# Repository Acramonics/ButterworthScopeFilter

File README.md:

ScopeFilter
===========

Andrew Martin, Acramonics, January 2026
---------------------------------------

This ScopeFilter is designed for putting in front of an oscilloscope
when doing audio work where there is HF interference from computers,
etc. It is a simple Active Butterworth dual 2nd order filter with a
cutoff of 50kHz.

It is powered by a standard 9v wallwart with the power supply section
taken from the Elektor ESR meter giving positive and negative 4.5v
rails.

Filter component values are calculated from
https://www.changpuak.ch/electronics/Butterworth_Lowpass_active_24dB.php
and tweaked to standard values. As specified, the filter starts to cut
off at 40kHz.

The `LTSpice` directory contains an LTSpice simulation showing the
frequency response. The Kicad Spice simulator seems to have difficulty
with dual rail power supplies.

The `FrontPanelDesigner` directory contains a simple front panel
layout for use with a small aluminium case (W:3.25" H:1.25" x D:4").
The software is available from schaeffer-ag.de/en/front-panel-designer

I built the filter without Molex 254s for any of the wires except the
power input. This is the only one that comes from the back making it
convenient (with long enough wires) to be able to take off the front
panel (which is closely connected to the PCB) and unplug the power
from the board.

These images are generated by Kicad:

With the exception of the two 100nF caps, I also ended up building the
board with 5mm ceramic caps in place of the box film caps shown.

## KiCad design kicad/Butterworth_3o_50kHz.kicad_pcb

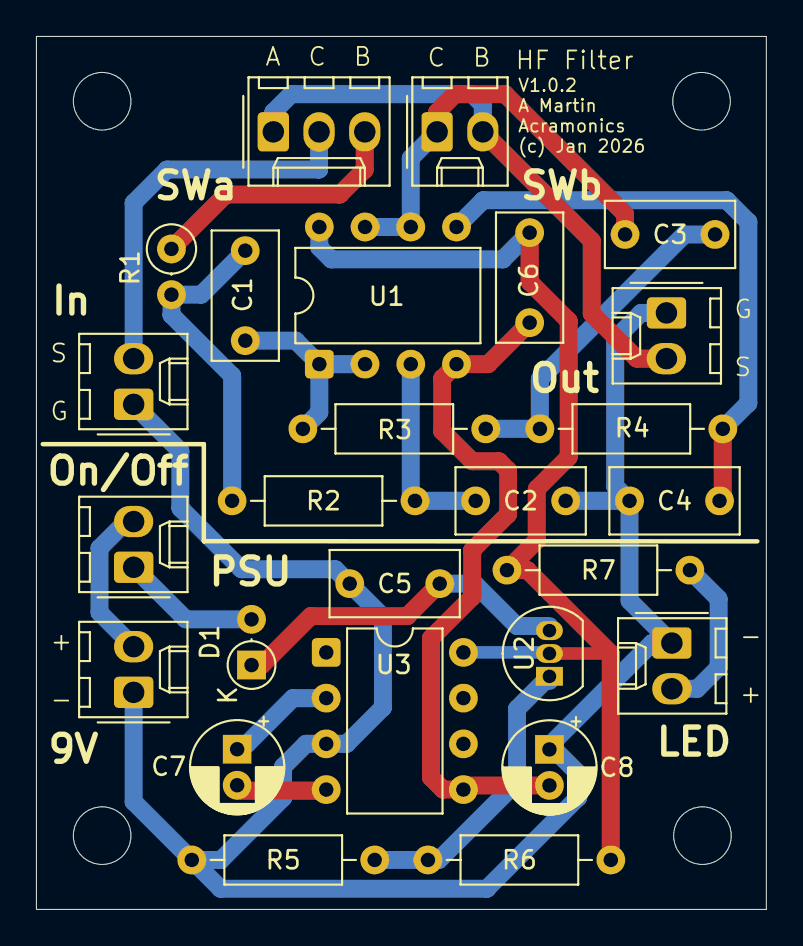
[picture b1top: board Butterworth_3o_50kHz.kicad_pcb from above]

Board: 2 copper layers, 40.6 x 48.5 mm, 26 parts (0 on the bottom side), 19 nets.

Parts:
C1, C2: 3.3nF; C_Rect_L7.0mm_W3.5mm_P5.00mm
C3: 8.2nF; C_Rect_L7.0mm_W3.5mm_P5.00mm
C4: 1.2nF; C_Rect_L7.0mm_W3.5mm_P5.00mm
C5, C6: 100nF; C_Rect_L7.0mm_W3.5mm_P5.00mm
C7: 10uF; CP_Radial_D5.0mm_P2.00mm
C8: 22uF; CP_Radial_D5.0mm_P2.00mm
D1: 1N4007; D_DO-35_SOD27_P2.54mm_Vertical_AnodeUp
J1, J2, J4, J5, J6, J7: Conn_01x02_Pin; Molex_KK-254_AE-6410-02A_1x02_P2.54mm_Vertical
J3: Conn_01x03_Pin; Molex_KK-254_AE-6410-03A_1x03_P2.54mm_Vertical
R1: 1K; R_Axial_DIN0207_L6.3mm_D2.5mm_P2.54mm_Vertical
R2, R3, R4: 1K; R_Axial_DIN0207_L6.3mm_D2.5mm_P10.16mm_Horizontal
R5: 680R; R_Axial_DIN0207_L6.3mm_D2.5mm_P10.16mm_Horizontal
R6: 220R; R_Axial_DIN0207_L6.3mm_D2.5mm_P10.16mm_Horizontal
R7: 330R; R_Axial_DIN0207_L6.3mm_D2.5mm_P10.16mm_Horizontal
U1: TL072; DIP-8_W7.62mm
U2: LM317L_TO92; TO-92_Inline
U3: LMC7660; DIP-8_W7.62mm

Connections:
0: C2.2, C4.2, C5.2, C8.1, J1.1, J2.1, J5.1, J7.1, R5.2, U3.3 (GND)
+5V: C6.2, R6.1, R7.1, U1.8 (V+), U2.2 (VO), U3.8 (V+)
-5V: C6.1, C8.2, U1.4 (V-), U3.5 (VOUT)
/in: J1.2, J3.2
/op1in: C2.1, R2.2, U1.3 (+)
/op1out: C1.2, R3.1, U1.1, U1.2 (-)
/op2in: C4.1, R4.2, U1.5 (+)
/out: C3.2, J4.1, U1.6 (-), U1.7
unnamed: C1.1, R1.2, R2.1
unnamed: C3.1, R3.2, R4.1
unnamed: D1.2 (A), J6.1
unnamed: C5.1, D1.1 (K), U2.3 (VI)
unnamed: J2.2, J3.1, J4.2
unnamed: J3.3, R1.1
unnamed: J5.2, J6.2
unnamed: J7.2, R7.2
unnamed: R5.1, R6.2, U2.1 (ADJ)
unnamed: C7.1, U3.2 (CAP+)
unnamed: C7.2, U3.4 (CAP-)

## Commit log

2026-02-06 Added PDF schematic and BOM
2026-02-22 Added annotation of the PSU section to the PCB
2026-02-24 Added front panel design, Gerber zip and pictures for README
2026-02-24 Fixed picture links
2026-02-24 Added images of the board from Kicad
2026-02-25 Corrected filenames to 50kHz instead of 40kHz
